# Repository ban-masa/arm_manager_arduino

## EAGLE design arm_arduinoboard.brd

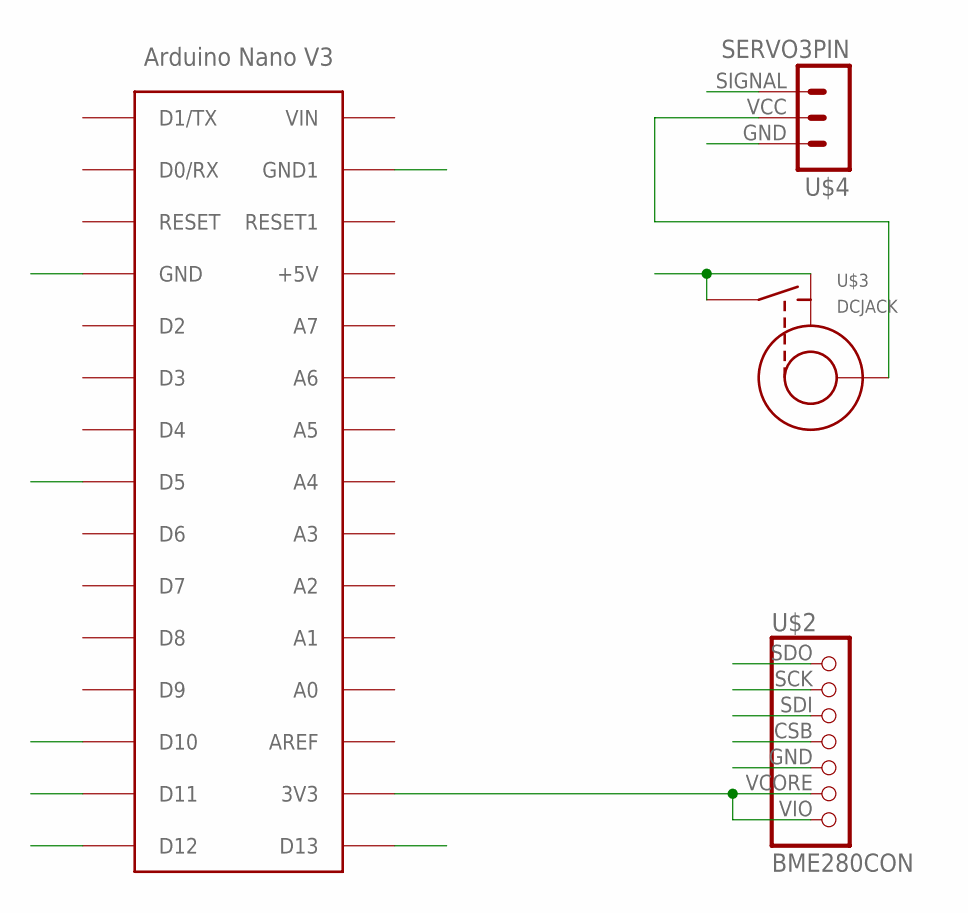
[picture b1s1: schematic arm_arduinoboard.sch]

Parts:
U$1: ARDUINO_NANO
U$2: BME280CON
U$3: DCJACK
U$4: SERVO3PIN

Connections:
CSB: U$1.D10, U$2.CSB
GND: U$1.GND, U$1.GND1, U$2.GND, U$3.P$2 (TIP), U$3.P$3 (SHUNT), U$4.GND
unnamed: U$1.3V3, U$2.VCORE, U$2.VIO
unnamed: U$3.P$1 (CENTER), U$4.VCC
SCK: U$1.D13, U$2.SCK
SDI: U$1.D11, U$2.SDI
SDO: U$1.D12, U$2.SDO
SIGNAL: U$1.D5, U$4.SIGNAL

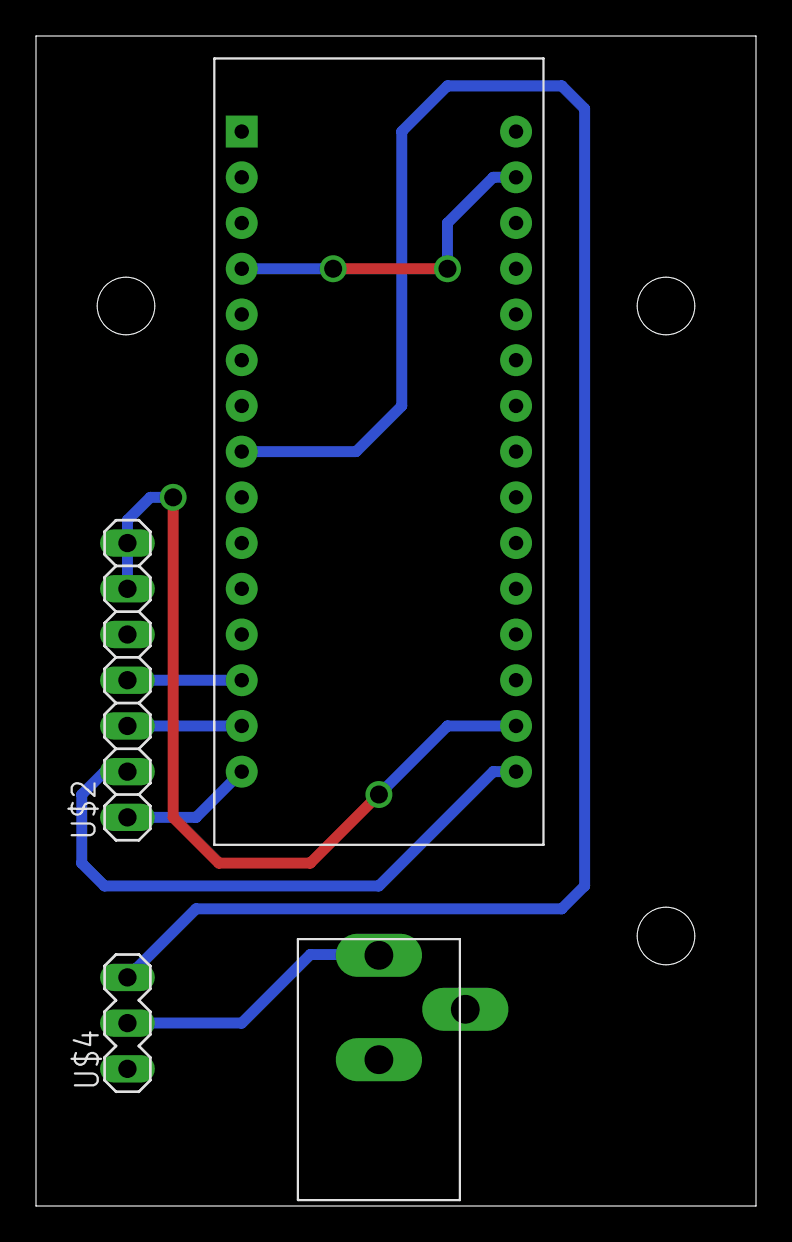
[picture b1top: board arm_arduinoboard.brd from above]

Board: 2 copper layers, 40.0 x 65.0 mm, 4 parts (0 on the bottom side), 8 nets.

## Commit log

2016-09-26 added APC_arm_arduinoboard.lbr arm_arduinoboard.brd arm_arduinoboard.sch
